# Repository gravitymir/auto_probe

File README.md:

# auto_probe

Отладочные core-платы на STM32 — исходники KiCad, гербера и генератор, который их собирает.

Платы не рисовались мышкой: схема, размещение, разводка и шелкография описаны Python-скриптами
поверх `pcbnew` API. Любую правку можно повторить одной командой, а результат каждый раз
прогоняется через набор проверок.

## Платы

| | STM32G474RE-CoreBoard | STM32H723ZG-CoreBoard |
|---|---|---|
| МК | STM32G474RET6, LQFP64 | STM32H723ZGT6, LQFP144 |
| Размер | 70 × 70 мм | 84 × 84 мм |
| Слоёв | 4 (GND / +3V3 внутренние) | 4 (GND / +3V3 внутренние) |
| Выводы | 4 × гребёнка 1×16, шаг 2.54 | 4 × гребёнка 2×18, шаг 2.54 |
| Питание | USB-C → AP2112K-3.3 | USB-C → AP2112K-3.3 |
| Кварцы | 8 МГц HSE + 32.768 кГц LSE | 25 МГц HSE + 32.768 кГц LSE |
| Отладка | 1×10, распиновка WeAct STLink V2.1 | 1×10, распиновка WeAct STLink V2.1 |
| Формат файлов | KiCad 7 | KiCad 10 |
| Статус | **готова к заказу** | **готова к заказу** |

Все выводы микроконтроллера выведены на гребёнки; шаг 2.54 мм — плата садится в макетку.
У H723 внутренние ряды гребёнок отстоят от центра ровно на 11 × 2.54 мм, то есть
противоположные гребёнки разнесены на 22 шага и плата ложится на сетку 0.1″.

## Что на плате (G474)

**Гребёнки.** J2 — левая, J3 — нижняя, J4 — правая, J5 — верхняя. Назначение каждого
контакта подписано на шелкографии и продублировано в [`PINOUT.csv`](boards/STM32G474RE-CoreBoard/PINOUT.csv).
На каждой гребёнке выведены GND и +3V3 — они подключены к внутренним полигонам через
thermal relief, отдельных дорожек к ним нет.

**J6 — разъём прошивки**, 1×10, распиновка один-в-один с WeAct MiniDebugger / STLink V2.1,
шлейф садится без переходников:

| 1 | 2 | 3 | 4 | 5 | 6 | 7 | 8 | 9 | 10 |
|---|---|---|---|---|---|---|---|---|---|
| 5V | GND | RX (PB6) | TX (PB7) | NRST | SWO (PB3) | GND | SWCLK | SWDIO | 3V3 |

> Контакт 1 (5V) связан с VBUS разъёма USB-C. **USB и отладчик одновременно не подключайте.**

**USB-C (J1)** — не только питание: D+/D− заведены на PA12/PA11, то есть на встроенный
USB 2.0 FS device. Через него работают USB CDC (виртуальный COM-порт) и штатный DFU-бутлоадер
STM32 — прошивка без отладчика вообще. CC1/CC2 притянуты 5.1 кОм к земле (роль устройства).

**Кнопки.** SW1 — RST, SW2 — BOOT0 (для входа в DFU: зажать BOOT, нажать RST).

**Светодиод.** D1 на PA5 (`LED_A`), через 1 кОм.

**R3 (0 Ω)** связывает +3V3 и +3V3A (VDDA / VREF+) в одной точке. Если АЦП будет шуметь —
на это же место ставится ферритовая бусина, переразводить ничего не нужно.

## Чем отличается H723

Раскладка повторяет G474: кристалл смещён к нижнему левому углу (`OFFX` / `OFFY` в
генераторе), поэтому верхнее и правое кольца шире — там и стоят светодиод, кнопки RST и
BOOT, разъём прошивки, USB-C и брендинг. USB-C стоит на плате целиком: корпус упирается
в контур, но за него не свисает.

Электрически устроена так же: те же гребёнки со всеми выводами, тот же USB-C с D+/D− на
встроенный USB FS (PA11/PA12), те же кнопки RST и BOOT0, светодиод (здесь на PB0 через
1 кОм), тот же R3 между +3V3 и +3V3A. Разъём прошивки J6 — тот же 1×10 с распиновкой
WeAct, но UART другой:

| 1 | 2 | 3 | 4 | 5 | 6 | 7 | 8 | 9 | 10 |
|---|---|---|---|---|---|---|---|---|---|
| 5V | GND | RX (PC10) | TX (PC11) | NRST | SWO (PB3) | GND | SWCLK | SWDIO | 3V3 |

Взят USART3 на PC10/PC11, а не USART1: у LQFP144 эта пара выходит на верхнюю гребёнку
рядом со SWCLK, тогда как PA9/PA10 попадают на правую гребёнку за коридором USB-C, куда
дорожку уже не проложить. Ещё из отличий: 25 МГц HSE вместо 8 МГц, две банки VCAP1/VCAP2
по 2.2 мкФ, отдельная развязка VDD33USB и 11 конденсаторов развязки под корпусом вместо 4.

HSE стоит в корпусе SMD-3225 с четырьмя падами: у JLCPCB 25 МГц в нём — Basic Part
(Yangxing X322525MOB4SI, `C9006`), тогда как двухпадовый 5032 только Extended и с
перебоями в наличии. Два лишних пада — экран корпуса, они связаны диагональю под
самим кварцем и посажены на полигон одной via. Нагрузочная ёмкость этого кварца
12 пФ, поэтому обвязка обоих генераторов — 18 пФ; кварц с другой CL ставить нельзя,
частота уйдёт.

Подписан каждый из 144 контактов, оба ряда. У J2, J3 и J5 ряды подписаны с разных сторон
гребёнки — внутренний изнутри, внешний снаружи. Напротив USB-C правое кольцо занято самим
разъёмом и его коридором, поэтому у J4 обе строки остаются слева. Подпись, которой не
хватило места, генератор сам переносит за гребёнку и сообщает об этом в отчёте сборки.
Полная карта — в [`PINOUT.csv`](boards/STM32H723ZG-CoreBoard/PINOUT.csv).

Шрифт шелкографии — 0.8 мм при толщине линии 0.15 мм: это минимум, который JLCPCB
печатает без расплывания. В кольце между гребёнкой и краем платы остаётся 3.7 мм, и
пятизначное имя таким шрифтом туда уже не входит — у нескольких цепей на шелке
короткая форма (`3V3A`, `PC2C`, `USBDP`). В цепях, схеме и `PINOUT.csv` имена полные.

Рядом с деталью печатается только обозначение: под корпусом МК банки развязки стоят
сеткой 3.2 мм, и номиналы читаемым шрифтом там просто не помещаются. Вместо этого на
обратной стороне, в свободных площадках у J4, напечатана таблица «обозначение —
номинал» на все 35 компонентов платы.

Схема H723 нарисована на листе A1: один символ LQFP144 занимает 76 × 188 мм, и вместе с
четырьмя гребёнками 2×18 и 26 конденсаторами на A2 (как у G474) он не раскладывается.

## Как открыть

Футпринты у обеих плат лежат в собственной библиотеке проекта `auto_probe.pretty` рядом с
платой и подключаются через `fp-lib-table` — системные библиотеки KiCad не нужны, и проект
не зависит от того, какая версия KiCad стоит у вас или у сборщика.

```
boards/STM32G474RE-CoreBoard/STM32G474RE-CoreBoard.kicad_pro
boards/STM32H723ZG-CoreBoard/STM32H723ZG-CoreBoard.kicad_pro
```

G474 сохранена в формате KiCad 7 (KiCad 8/9/10 открывают её и конвертируют при первом
сохранении), H723 — в формате KiCad 10: её собирали уже им. Платы независимы, так что
разные форматы никому не мешают, но KiCad 7 файл H723 не откроет.

## Как заказать

Для JLCPCB / PCBWay достаточно одного архива:

```
boards/STM32G474RE-CoreBoard/STM32G474RE-CoreBoard_gerbers.zip
boards/STM32H723ZG-CoreBoard/STM32H723ZG-CoreBoard_gerbers.zip
```

Внутри: 4 слоя меди, паяльная маска, шелкография, паста, контур платы (`.gm1`) и сверловка
(PTH / NPTH раздельно). Параметры заказа: 4 слоя, 1.6 мм, HASL или ENIG, минимальный
зазор 0.2 мм, минимальное отверстие 0.2 мм.

Для монтажа на заводе — `BOM.csv` и `pos.csv` рядом с платой. В BOM G474 проставлены
номера LCSC для микроконтроллера, стабилизатора и USB-C; у H723 — для стабилизатора и
USB-C, номер самого STM32H723ZGT6 подставьте сами. Пассивку подберите из JLCPCB Basic
Parts по номиналу и типоразмеру.

## Генератор

```
gen/
├── kigen.py        разбор библиотек символов, генерация .kicad_sch
├── pcbhelp.py      обёртка над pcbnew: размещение, дорожки, via, полигоны, текст
├── kicadenv.py     где лежат библиотеки KiCad и различия API между версиями
├── build_g474.py   сборка платы G474 целиком
├── build_h723.py   сборка платы H723
├── outputs.py      BOM.csv и PINOUT.csv из готовой платы
├── export.py       гербера, сверловка, pos.csv, PDF и архив для завода
├── drc.py          геометрический контроль зазоров + несоединённые цепи
├── conn.py         связность цепей (union-find)
├── crtyd.py        пересечения courtyard
└── silkchk.py      наложения шелкографии и печать поверх падов
```

Нужен Python с модулем `pcbnew` — от KiCad 7 или KiCad 10 (в Debian/Ubuntu — пакет
`kicad`, в Windows — `C:\Program Files\KiCad\10.0\bin\python.exe`). Каталоги системных
библиотек скрипты находят сами:

```bash
python3 gen/build_h723.py boards/STM32H723ZG-CoreBoard
python3 gen/outputs.py    boards/STM32H723ZG-CoreBoard/STM32H723ZG-CoreBoard.kicad_pcb
python3 gen/export.py     boards/STM32H723ZG-CoreBoard
python3 gen/drc.py        boards/STM32H723ZG-CoreBoard/STM32H723ZG-CoreBoard.kicad_pcb
python3 gen/silkchk.py    boards/STM32H723ZG-CoreBoard/STM32H723ZG-CoreBoard.kicad_pcb
```

`export.py` зовёт `kicad-cli`; им же гоняется штатный DRC:

```bash
kicad-cli pcb drc --schematic-parity --severity-error boards/STM32H723ZG-CoreBoard/STM32H723ZG-CoreBoard.kicad_pcb
```

Позиции надписей, выставленные вручную в KiCad, хранятся в `build_g474.py` в таблицах
`REF_AT` и `VAL_AT` — пересборка их не затирает. Остальные надписи расставляет автоподбор,
который считает занятыми чужие надписи, контуры, **пады** (шелк поверх открытой меди не
печатается) и **корпуса деталей** (иначе надпись уезжает под чип и её не видно).

## Проверки

У KiCad 7 в CLI нет DRC, поэтому проверки написаны отдельно. Текущее состояние обеих плат:

| проверка | G474 | H723 |
|---|---|---|
| зазоры меди | 0 нарушений при штатных 0.2 мм | 0 нарушений при штатных 0.2 мм |
| DRC самого KiCad | 0 ошибок | 0 ошибок |
| схема против платы | — | 0 расхождений |
| несоединённые цепи | 0 | 0 |
| пересечения courtyard | 0 | 0 |
| отверстие-отверстие | минимум 0.387 мм | минимум 0.278 мм |
| наложения шелкографии | 0 | 0 |
| шелкография поверх падов | 0 | 0 |

Обе платы проходят штатный DRC самого KiCad (проверено в KiCad 10) — 0 ошибок при netclass
clearance 0.2 мм. Сигнальные дорожки 0.15 мм, силовые 0.35 мм; минимум JLCPCB для этого
процесса — 0.09 мм. У H723 есть ещё и проверка схемы против платы (`--schematic-parity`),
её умеет только CLI KiCad 10.

Веер из 144 выводов на четыре гребёнки 2×18 упирается не в ширину дорожки, а в угол:
крайние дорожки идут под 42°, и поперёк соседа от шага 0.5 мм остаётся 0.5·cos42° = 0.37 мм.
Отсюда и вынос гребёнок на 27.94 мм от центра — на 26 мм веер в зазор 0.2 мм не укладывался
ни при какой разумной ширине.

## Что осталось

- На D+/D− нет защиты от статики (например, USBLC6-2SC6) — для прототипа терпимо.
- D+/D− заодно выведены на J4 контакты 3 и 4. Удобно для отладки, но это отвод на
  дифференциальной паре: если USB начнёт капризничать при определении — снимите с них всё.
- VBUS не заведён на вывод МК, определить подключение кабеля программно нельзя.

## Лицензия

MIT — см. [LICENSE](LICENSE).

Референсные материалы ST (схемы Nucleo MB1367 / MB1364, их гербера и BOM) в репозиторий
не включены: они распространяются по ST Open Platform License Agreement. Разбор того, что
из них полезно и как это открыть в KiCad, — в [docs/](docs/).

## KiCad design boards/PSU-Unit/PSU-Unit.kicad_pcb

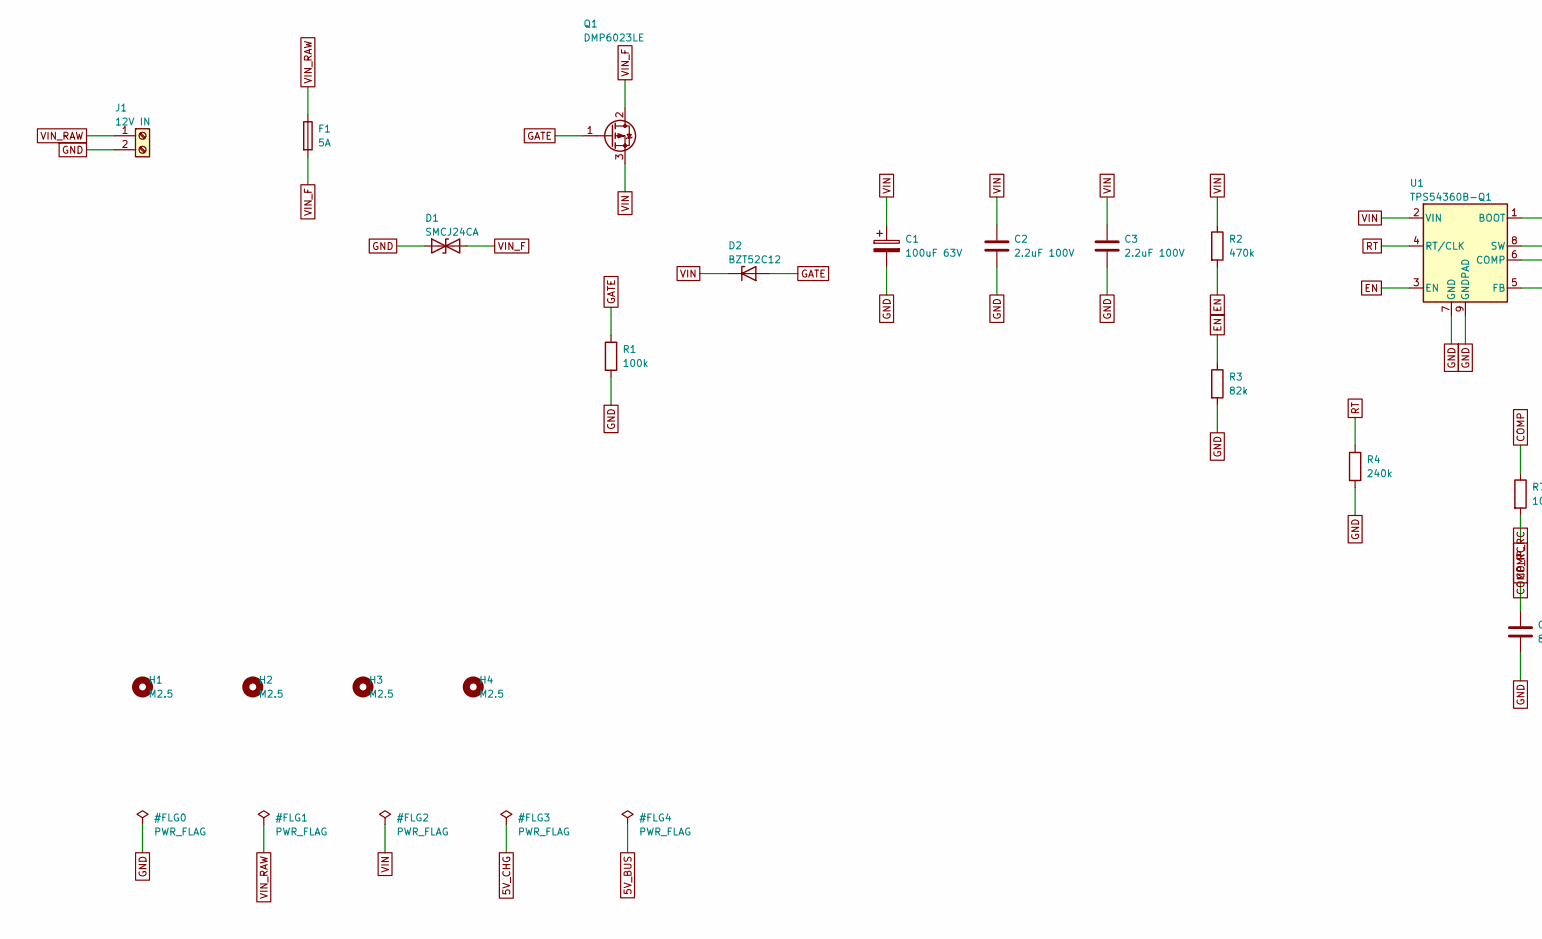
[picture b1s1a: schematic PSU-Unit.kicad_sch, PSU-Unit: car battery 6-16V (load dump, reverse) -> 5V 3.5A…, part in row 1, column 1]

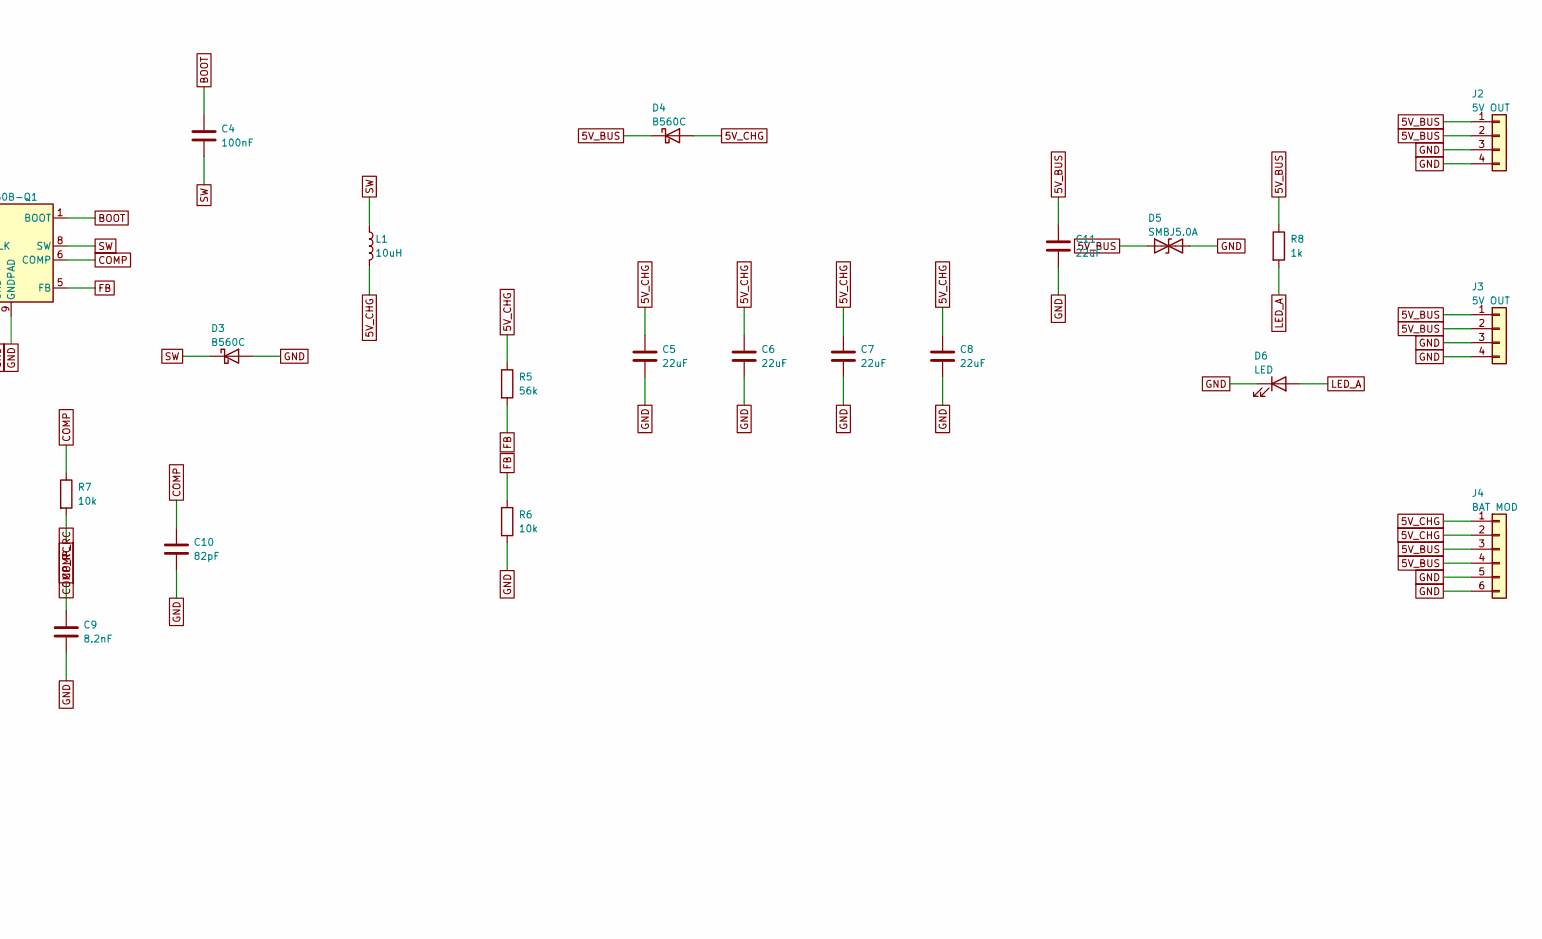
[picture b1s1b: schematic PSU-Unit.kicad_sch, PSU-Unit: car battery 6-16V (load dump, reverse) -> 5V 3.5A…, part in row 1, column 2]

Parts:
C1: 100uF 63V; CP_Elec_10x10
C2, C3: 2.2uF 100V; C_1210_3225Metric
C4: 100nF; C_0402_1005Metric
C5, C6, C7, C8, C11: 22uF; C_1206_3216Metric
C9: 8.2nF; C_0402_1005Metric
C10: 82pF; C_0402_1005Metric
D1: SMCJ24CA; D_SMC
D2: BZT52C12; D_SOD-123
D3, D4: B560C; D_SMC
D5: SMBJ5.0A; D_SMB
D6: LED; LED_0805_2012Metric
F1: 5A; Fuse_Littelfuse_451_2410
H1, H2, H3, H4: M2.5; MountingHole_2.7mm_M2.5
J1: 12V IN; TerminalBlock_Phoenix_MKDS-1,5-2_1x02_P5.00mm_Horizontal
J2, J3: 5V OUT; JST_PH_B4B-PH-K_1x04_P2.00mm_Vertical
J4: BAT MOD; JST_PH_B6B-PH-K_1x06_P2.00mm_Vertical
L1: 10uH; L_TDK_SPM10065VT
Q1: DMP6023LE; SOT-223-3_TabPin2
R1: 100k; R_0402_1005Metric
R2: 470k; R_0402_1005Metric
R3: 82k; R_0402_1005Metric
R4: 240k; R_0402_1005Metric
R5: 56k; R_0402_1005Metric
R6, R7: 10k; R_0402_1005Metric
R8: 1k; R_0402_1005Metric
U1: TPS54360B-Q1; TI_SO-PowerPAD-8_ThermalVias

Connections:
5V_BUS: C11.1, D4.1 (K), D5.1 (A1), J2.1, J2.2, J3.1, J3.2, J4.3, J4.4, R8.1
5V_CHG: C5.1, C6.1, C7.1, C8.1, D4.2 (A), J4.1, J4.2, L1.2, R5.1
BOOT: C4.1, U1.1 (BOOT)
COMP: C10.1, R7.1, U1.6 (COMP)
COMP_RC: C9.1, R7.2
EN: R2.2, R3.1, U1.3 (EN)
FB: R5.2, R6.1, U1.5 (FB)
GATE: D2.2 (A), Q1.1 (G), R1.1
GND: C1.2, C2.2, C3.2, C5.2, C6.2, C7.2, C8.2, C9.2, C10.2, C11.2, D1.1 (A1), D3.2 (A), D5.2 (A2), D6.1 (K), J1.2, J2.3, J2.4, J3.3, J3.4, J4.5, J4.6, R1.2, R3.2, R4.2, R6.2, U1.7 (GND), U1.9 (GNDPAD)
LED_A: D6.2 (A), R8.2
RT: R4.1, U1.4 (RT/CLK)
SW: C4.2, D3.1 (K), L1.1, U1.8 (SW)
VIN: C1.1, C2.1, C3.1, D2.1 (K), Q1.3 (S), R2.1, U1.2 (VIN)
VIN_F: D1.2 (A2), F1.2, Q1.2 (D)
VIN_RAW: F1.1, J1.1

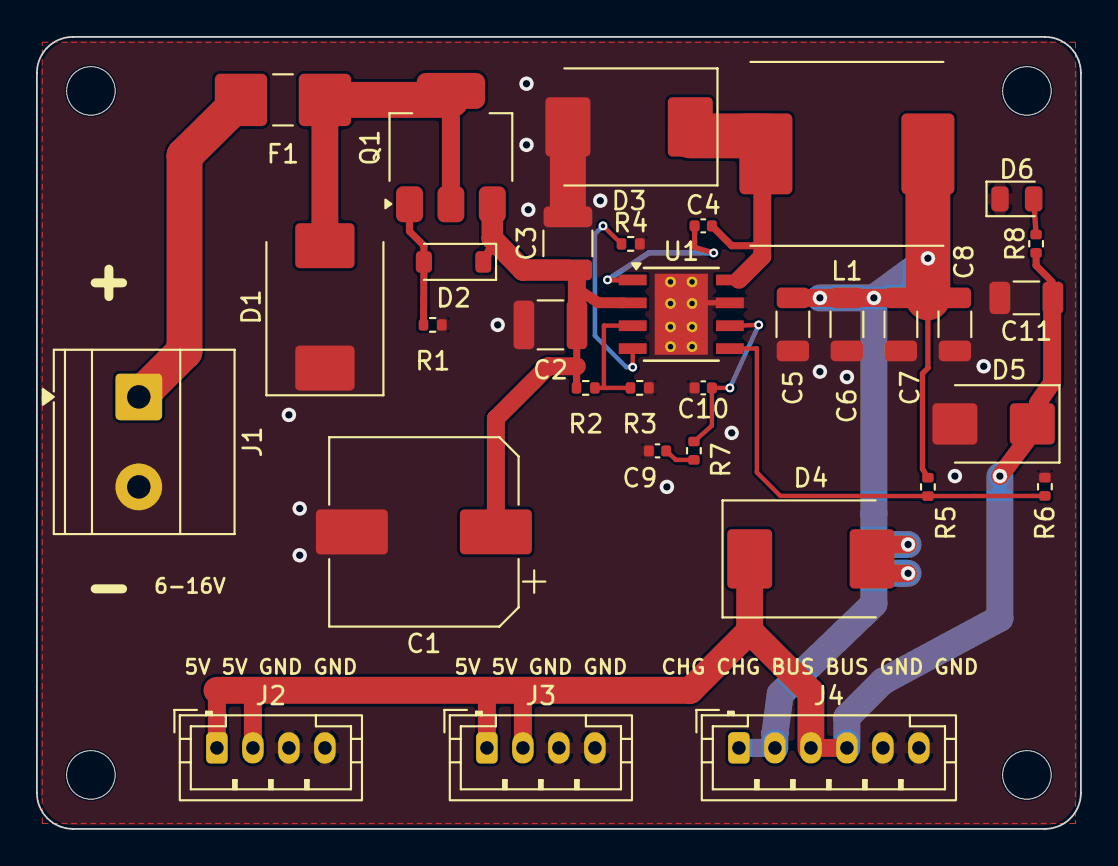
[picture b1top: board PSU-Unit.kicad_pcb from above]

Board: 2 copper layers, 58.0 x 44.0 mm, 37 parts (0 on the bottom side), 15 nets.

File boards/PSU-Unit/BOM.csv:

Comment,Designator,Footprint,LCSC Part #,Qty,Note
100uF 63V,C1,auto_probe:CP_Elec_10x10,C28241,1,проверить наличие на складе
100nF,C4,auto_probe:C_0402_1005Metric,C1525,1,проверить наличие на складе
8.2nF,C9,auto_probe:C_0402_1005Metric,C45186,1,проверить наличие на складе
82pF,C10,auto_probe:C_0402_1005Metric,C45501,1,проверить наличие на складе
22uF,"C11,C5,C6,C7,C8",auto_probe:C_1206_3216Metric,C12891,5,проверить наличие на складе
2.2uF 100V,"C2,C3",auto_probe:C_1210_3225Metric,C55151,2,проверить наличие на складе
SMBJ5.0A,D5,auto_probe:D_SMB,C110528,1,проверить наличие на складе
SMCJ24CA,D1,auto_probe:D_SMC,C151279,1,проверить наличие на складе
B560C,"D3,D4",auto_probe:D_SMC,C85100,2,проверить наличие на складе
BZT52C12,D2,auto_probe:D_SOD-123,C124196,1,проверить наличие на складе
5A,F1,auto_probe:Fuse_Littelfuse_451_2410,C48467,1,проверить наличие на складе
5V OUT,"J2,J3",auto_probe:JST_PH_B4B-PH-K_1x04_P2.00mm_Vertical,C131334,2,проверить наличие на складе
BAT MOD,J4,auto_probe:JST_PH_B6B-PH-K_1x06_P2.00mm_Vertical,C131342,1,проверить наличие на складе
LED,D6,auto_probe:LED_0805_2012Metric,C84256,1,проверить наличие на складе
10uH,L1,auto_probe:L_TDK_SPM10065VT,C5119327,1,проверить наличие на складе
1k,R8,auto_probe:R_0402_1005Metric,C11702,1,проверить наличие на складе
100k,R1,auto_probe:R_0402_1005Metric,C25741,1,проверить наличие на складе
10k,"R6,R7",auto_probe:R_0402_1005Metric,C25744,2,проверить наличие на складе
470k,R2,auto_probe:R_0402_1005Metric,C25790,1,проверить наличие на складе
56k,R5,auto_probe:R_0402_1005Metric,C25796,1,проверить наличие на складе
82k,R3,auto_probe:R_0402_1005Metric,C4142,1,проверить наличие на складе
240k,R4,auto_probe:R_0402_1005Metric,C64043,1,проверить наличие на складе
DMP6023LE,Q1,auto_probe:SOT-223-3_TabPin2,C154901,1,проверить наличие на складе
TPS54360B-Q1,U1,auto_probe:TI_SO-PowerPAD-8_ThermalVias,C2687968,1,проверить наличие на складе
12V IN,J1,"auto_probe:TerminalBlock_Phoenix_MKDS-1,5-2_1x02_P5.00mm_Horizontal",C474881,1,проверить наличие на складе

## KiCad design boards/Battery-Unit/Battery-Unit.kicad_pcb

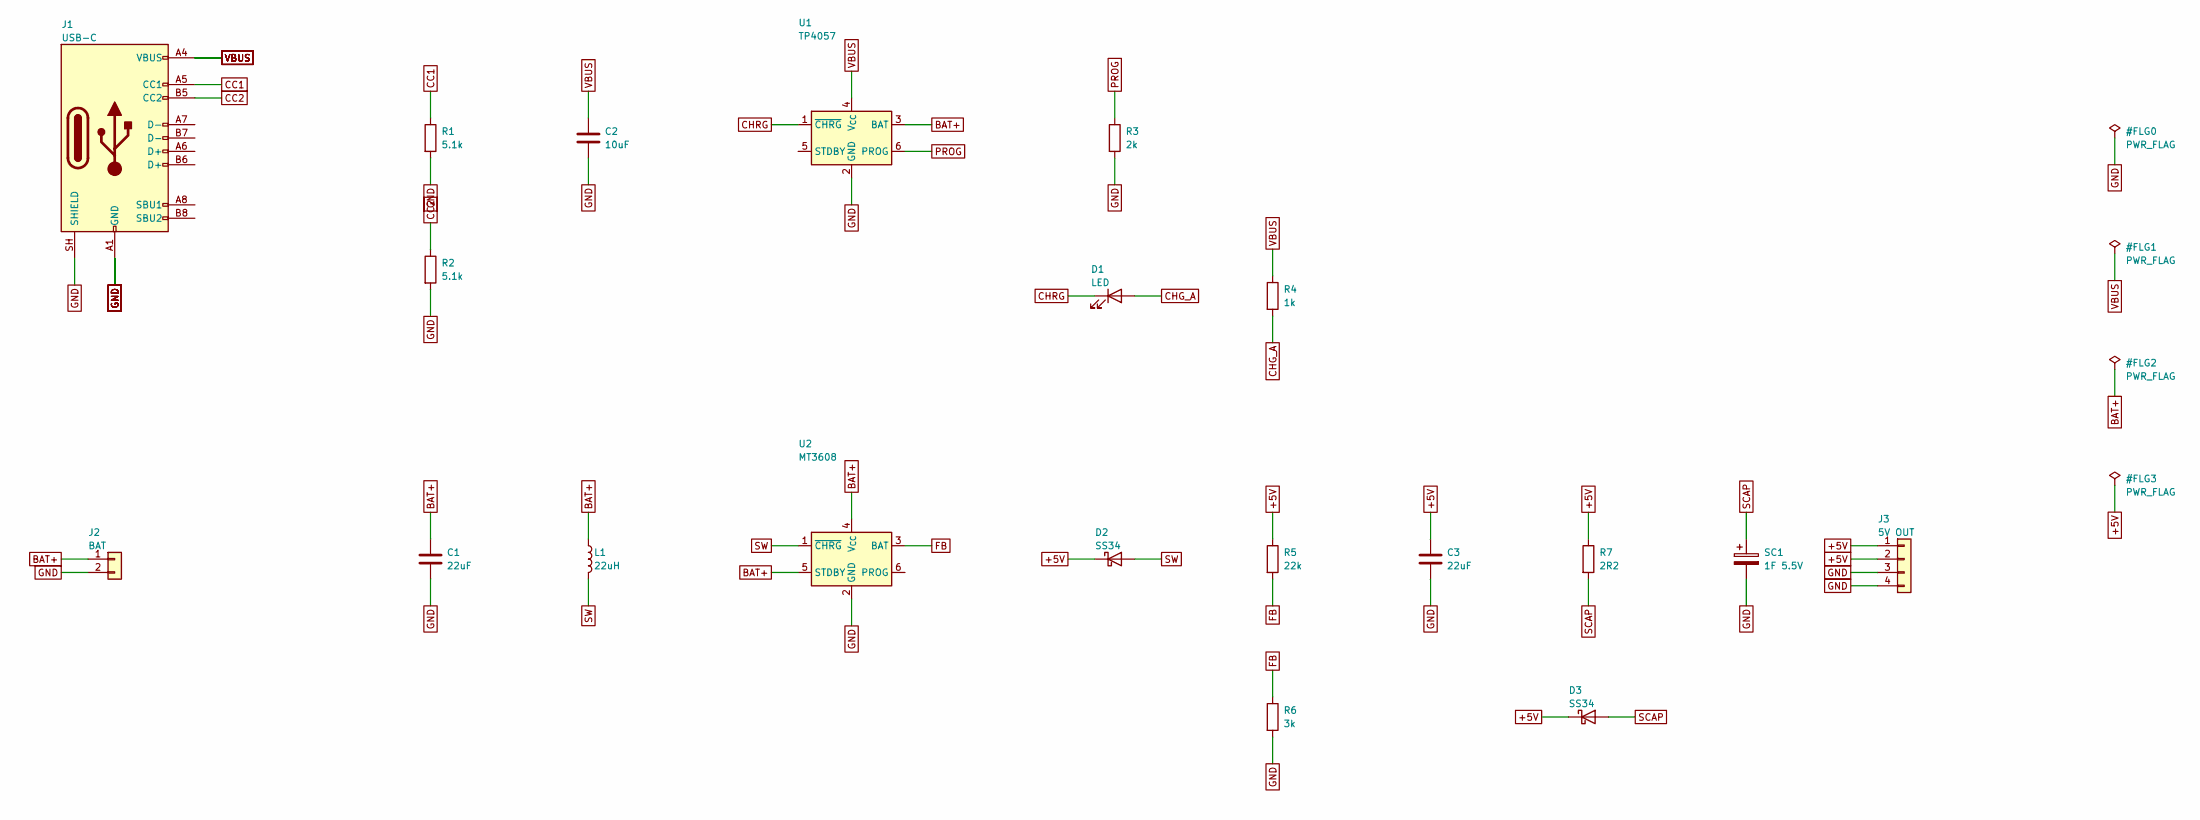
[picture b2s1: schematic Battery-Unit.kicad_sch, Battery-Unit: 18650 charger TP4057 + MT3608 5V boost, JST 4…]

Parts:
C1, C3: 22uF; C_0805_2012Metric
C2: 10uF; C_0805_2012Metric
D1: LED; LED_0805_2012Metric
D2, D3: SS34; D_SMA
J1: USB-C; USB_C_Receptacle_HRO_TYPE-C-31-M-12
J2: BAT; JST_PH_B2B-PH-K_1x02_P2.00mm_Vertical
J3: 5V OUT; JST_PH_B4B-PH-K_1x04_P2.00mm_Vertical
L1: 22uH; L_Taiyo-Yuden_NR-40xx
R1, R2: 5.1k; R_0402_1005Metric
R3: 2k; R_0402_1005Metric
R4: 1k; R_0402_1005Metric
R5: 22k; R_0402_1005Metric
R6: 3k; R_0402_1005Metric
R7: 2R2; R_0402_1005Metric
SC1: 1F 5.5V; CP_Radial_D10.0mm_P5.00mm
U1: TP4057; SOT-23-6
U2: MT3608; SOT-23-6

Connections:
+5V: C3.1, D2.1 (K), D3.1 (K), J3.1, J3.2, R5.1, R7.1
BAT+: C1.1, J2.1, L1.1, U1.3 (BAT), U2.4 (V_{CC}), U2.5 (STDBY)
CC1: J1.A5 (CC1), R1.1
CC2: J1.B5 (CC2), R2.1
CHG_A: D1.2 (A), R4.2
CHRG: D1.1 (K), U1.1 (~CHRG)
FB: R5.2, R6.1, U2.3 (BAT)
GND: C1.2, C2.2, C3.2, J1.A1 (GND), J1.A12 (GND), J1.B1 (GND), J1.B12 (GND), J1.SH (SHIELD), J2.2, J3.3, J3.4, R1.2, R2.2, R3.2, R6.2, SC1.2, U1.2 (GND), U2.2 (GND)
PROG: R3.1, U1.6 (PROG)
SCAP: D3.2 (A), R7.2, SC1.1
SW: D2.2 (A), L1.2, U2.1 (~CHRG)
VBUS: C2.1, J1.A4 (VBUS), J1.A9 (VBUS), J1.B4 (VBUS), J1.B9 (VBUS), R4.1, U1.4 (V_{CC})

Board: 2 copper layers, 20 parts (0 on the bottom side), 12 nets, no tracks yet.

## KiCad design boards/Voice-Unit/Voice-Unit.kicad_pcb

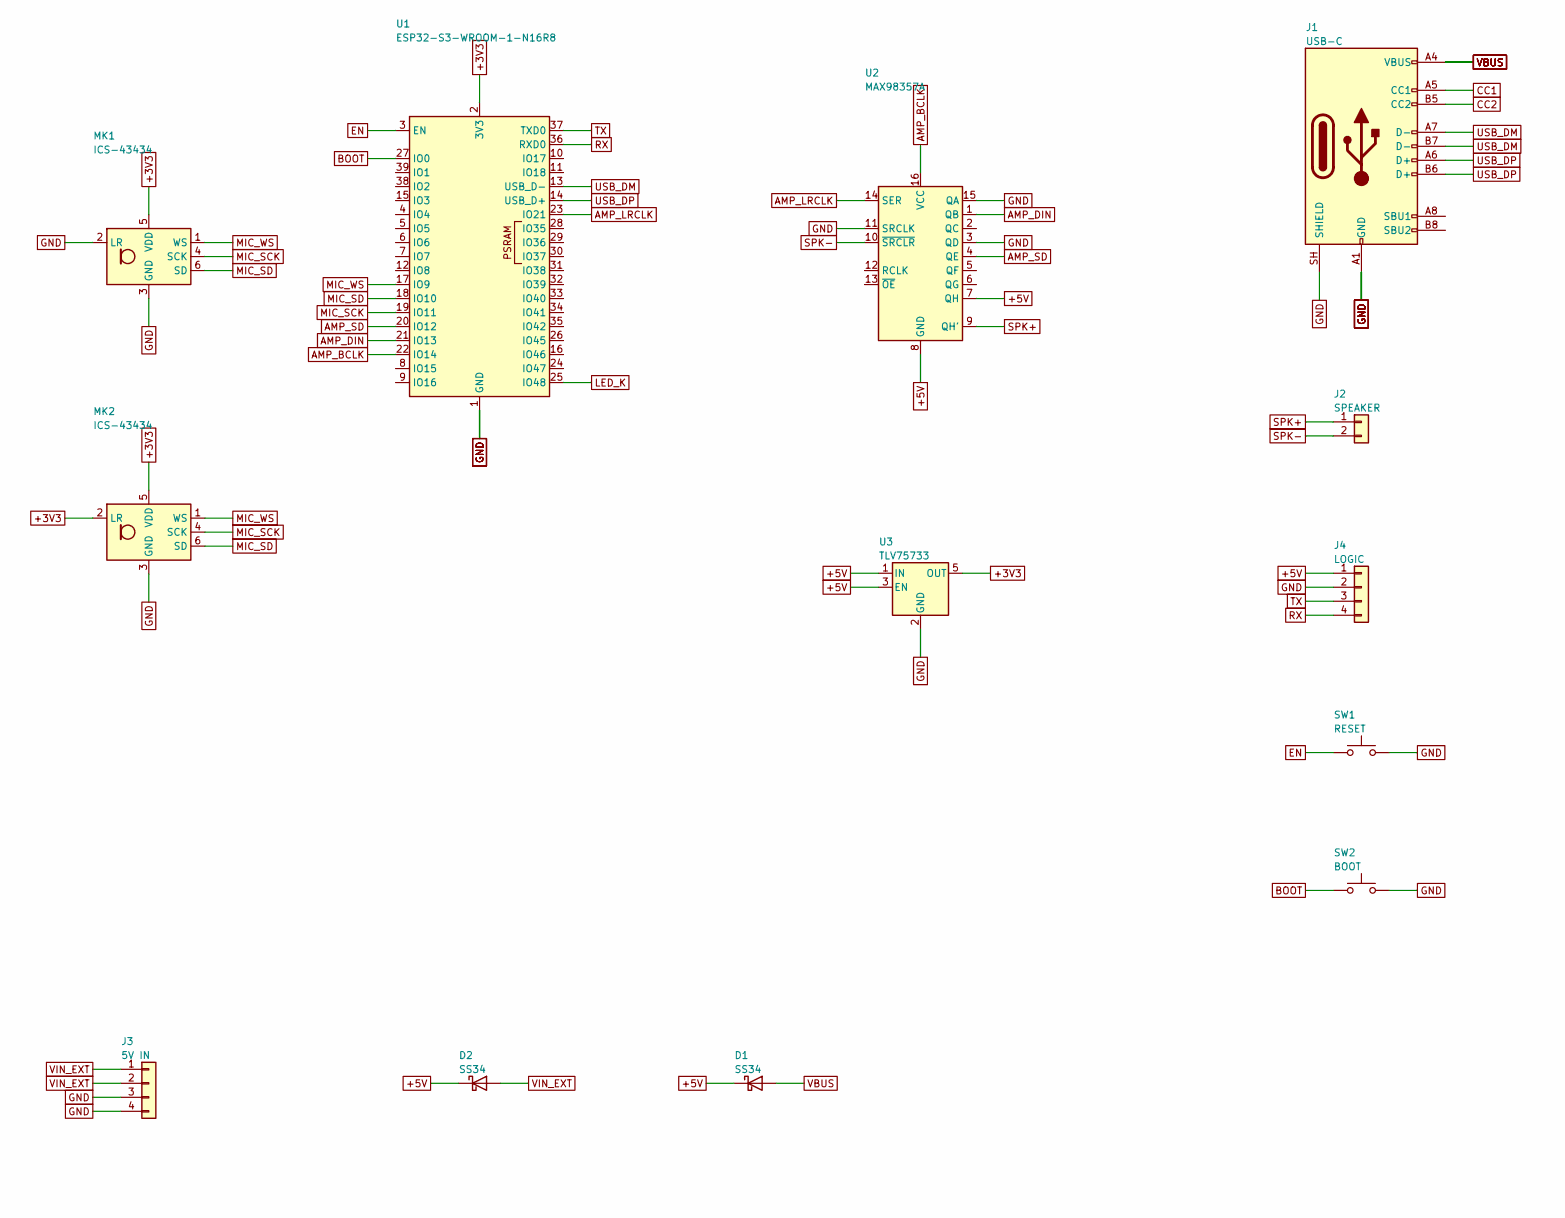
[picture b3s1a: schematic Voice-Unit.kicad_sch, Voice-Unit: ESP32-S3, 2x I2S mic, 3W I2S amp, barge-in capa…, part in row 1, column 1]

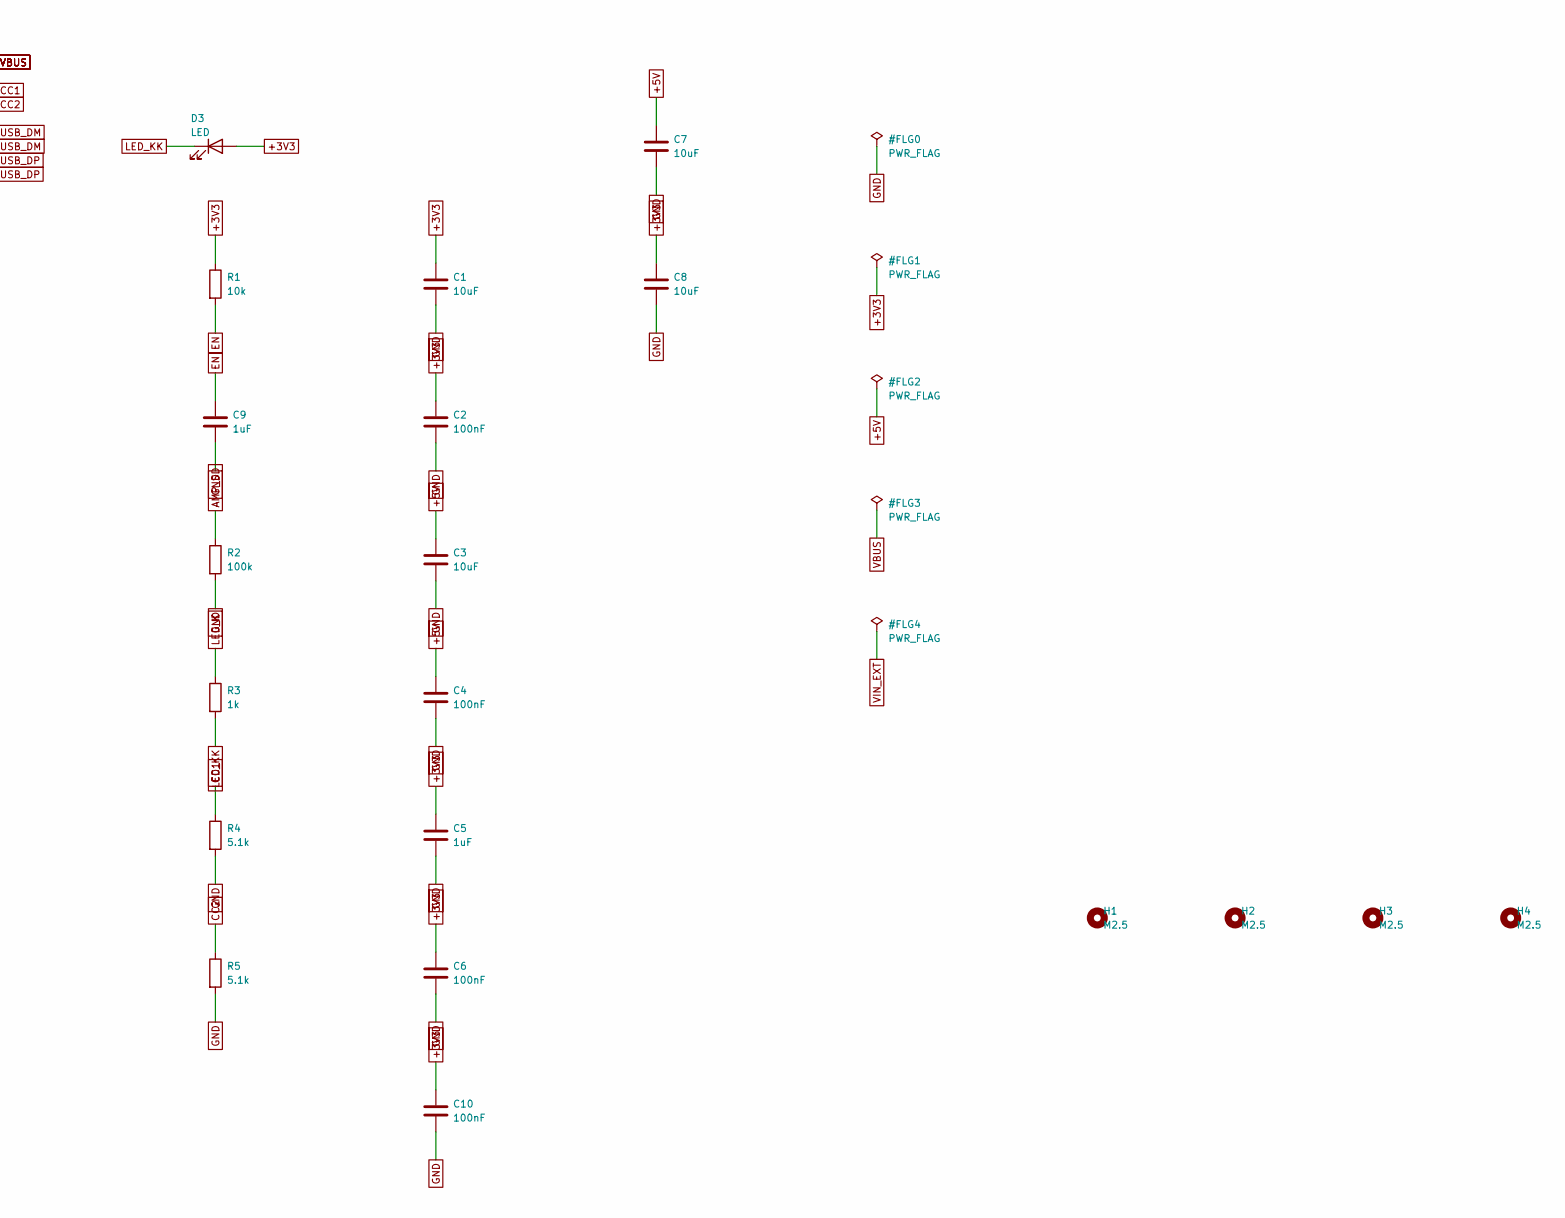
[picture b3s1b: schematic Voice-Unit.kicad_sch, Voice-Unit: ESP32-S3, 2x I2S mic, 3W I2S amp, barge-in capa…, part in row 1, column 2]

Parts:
C1, C3, C7, C8: 10uF; C_0805_2012Metric
C2, C4, C6, C10: 100nF; C_0402_1005Metric
C5, C9: 1uF; C_0402_1005Metric
D1, D2: SS34; D_SMA
D3: LED; LED_0805_2012Metric
H1, H2, H3, H4: M2.5; MountingHole_2.7mm_M2.5
J1: USB-C; USB_C_Receptacle_HRO_TYPE-C-31-M-12
J2: SPEAKER; PinHeader_1x02_P2.54mm_Vertical
J3: 5V IN; JST_PH_B4B-PH-K_1x04_P2.00mm_Vertical
J4: LOGIC; PinHeader_1x04_P2.54mm_Vertical
MK1, MK2: ICS-43434; InvenSense_ICS-43434-6_3.5x2.65mm
R1: 10k; R_0402_1005Metric
R2: 100k; R_0402_1005Metric
R3: 1k; R_0402_1005Metric
R4, R5: 5.1k; R_0402_1005Metric
SW1: RESET; SW_SPST_SKQG_WithoutStem
SW2: BOOT; SW_SPST_SKQG_WithoutStem
U1: ESP32-S3-WROOM-1-N16R8; ESP32-S3-WROOM-1
U2: MAX98357A; TQFN-16-1EP_3x3mm_P0.5mm_EP1.6x1.6mm
U3: TLV75733; SOT-23-5

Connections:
+3V3: C1.1, C2.1, C5.1, C6.1, C8.1, C10.1, D3.2 (A), MK1.5 (VDD), MK2.2 (LR), MK2.5 (VDD), R1.1, U1.2 (3V3), U3.5 (OUT)
+5V: C3.1, C4.1, C7.1, D1.1 (K), D2.1 (K), J4.1, U2.7 (QH), U2.8 (GND), U3.1 (IN), U3.3 (EN)
AMP_BCLK: U1.22 (IO14), U2.16 (VCC)
AMP_DIN: U1.21 (IO13), U2.1 (QB)
AMP_LRCLK: U1.23 (IO21), U2.14 (SER)
AMP_SD: R2.1, U1.20 (IO12), U2.4 (QE)
BOOT: SW2.1, U1.27 (IO0)
CC1: J1.A5 (CC1), R4.1
CC2: J1.B5 (CC2), R5.1
EN: C9.1, R1.2, SW1.1, U1.3 (EN)
GND: C1.2, C2.2, C3.2, C4.2, C5.2, C6.2, C7.2, C8.2, C9.2, C10.2, J1.A1 (GND), J1.A12 (GND), J1.B1 (GND), J1.B12 (GND), J1.SH (SHIELD), J3.3, J3.4, J4.2, MK1.2 (LR), MK1.3 (GND), MK2.3 (GND), R2.2, R4.2, R5.2, SW1.2, SW2.2, U1.1 (GND), U1.40 (GND), U1.41 (GND), U2.3 (QD), U2.11 (SRCLK), U2.15 (QA), U2.17, U3.2 (GND)
LED_K: R3.1, U1.25 (IO48)
LED_KK: D3.1 (K), R3.2
MIC_SCK: MK1.4 (SCK), MK2.4 (SCK), U1.19 (IO11)
MIC_SD: MK1.6 (SD), MK2.6 (SD), U1.18 (IO10)
MIC_WS: MK1.1 (WS), MK2.1 (WS), U1.17 (IO9)
RX: J4.4, U1.36 (RXD0)
SPK+: J2.1, U2.9 (QH')
SPK-: J2.2, U2.10 (~SRCLR)
TX: J4.3, U1.37 (TXD0)
USB_DM: J1.A7 (D-), J1.B7 (D-), U1.13 (USB_D-)
USB_DP: J1.A6 (D+), J1.B6 (D+), U1.14 (USB_D+)
VBUS: D1.2 (A), J1.A4 (VBUS), J1.A9 (VBUS), J1.B4 (VBUS), J1.B9 (VBUS)
VIN_EXT: D2.2 (A), J3.1, J3.2

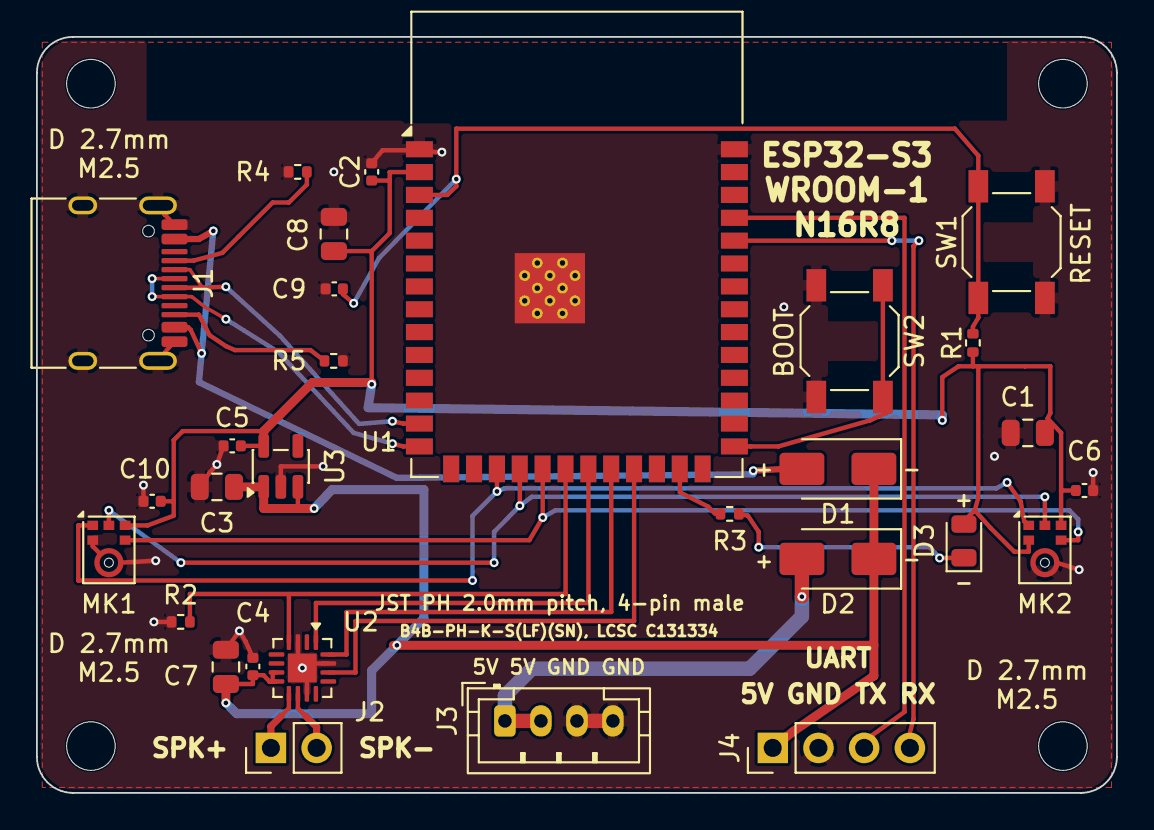
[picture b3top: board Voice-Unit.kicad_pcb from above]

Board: 2 copper layers, 60.0 x 42.0 mm, 33 parts (0 on the bottom side), 24 nets.

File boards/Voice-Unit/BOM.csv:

Comment,Designator,Footprint,LCSC Part #,Qty,Note
100nF,"C10,C2,C4,C6",auto_probe:C_0402_1005Metric,C1525,4,проверить наличие на складе
1uF,"C5,C9",auto_probe:C_0402_1005Metric,C52923,2,проверить наличие на складе
10uF,"C1,C3,C7,C8",auto_probe:C_0805_2012Metric,C15850,4,проверить наличие на складе
SS34,"D1,D2",auto_probe:D_SMA,C8678,2,проверить наличие на складе
ESP32-S3-WROOM-1-N16R8,U1,auto_probe:ESP32-S3-WROOM-1,C2913202,1,проверить наличие на складе
ICS-43434,"MK1,MK2",auto_probe:InvenSense_ICS-43434-6_3.5x2.65mm,C5656610,2,проверить наличие на складе
5V IN,J3,auto_probe:JST_PH_B4B-PH-K_1x04_P2.00mm_Vertical,C131334,1,проверить наличие на складе
LED,D3,auto_probe:LED_0805_2012Metric,C84256,1,проверить наличие на складе
SPEAKER,J2,auto_probe:PinHeader_1x02_P2.54mm_Vertical,,1,"выводная: в SMT-монтаж не идёт, паяется отдельно"
LOGIC,J4,auto_probe:PinHeader_1x04_P2.54mm_Vertical,,1,"выводная: в SMT-монтаж не идёт, паяется отдельно"
1k,R3,auto_probe:R_0402_1005Metric,C11702,1,проверить наличие на складе
100k,R2,auto_probe:R_0402_1005Metric,C25741,1,проверить наличие на складе
10k,R1,auto_probe:R_0402_1005Metric,C25744,1,проверить наличие на складе
5.1k,"R4,R5",auto_probe:R_0402_1005Metric,C25905,2,проверить наличие на складе
TLV75733,U3,auto_probe:SOT-23-5,C485517,1,проверить наличие на складе
BOOT/RESET,"SW1,SW2",auto_probe:SW_SPST_SKQG_WithoutStem,C318884,2,проверить наличие на складе
MAX98357A,U2,auto_probe:TQFN-16-1EP_3x3mm_P0.5mm_EP1.6x1.6mm,C910544,1,проверить наличие на складе
USB-C,J1,auto_probe:USB_C_Receptacle_HRO_TYPE-C-31-M-12,C165948,1,проверить наличие на складе

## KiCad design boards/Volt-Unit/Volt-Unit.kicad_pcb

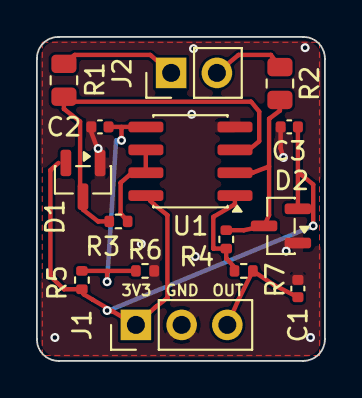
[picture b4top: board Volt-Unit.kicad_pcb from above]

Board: 2 copper layers, 16.0 x 18.0 mm, 15 parts (0 on the bottom side), 10 nets.

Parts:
C1: 470pF; C_0402_1005Metric
C2, C3: 100nF; C_0402_1005Metric
D1, D2: BAT54S; SOT-23
J1: LOGIC; PinHeader_1x03_P2.54mm_Vertical
J2: PROBE; PinHeader_1x02_P2.54mm_Vertical
R1, R2: 470k; R_0805_2012Metric
R3, R4: 18k; R_0402_1005Metric
R5, R6: 10k; R_0402_1005Metric
R7: 220R; R_0402_1005Metric
U1: LMV358; SOIC-8_3.9x4.9mm_P1.27mm

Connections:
+3V3: C3.1, D1.2, D2.2, J1.1, R5.1, U1.8
AOUT: R4.2, R7.1, U1.1
FB: D2.3, R2.2, R4.1, U1.2
GND: C1.2, C2.2, C3.2, D1.1, D2.1, J1.2, R6.2, U1.4
INP: D1.3, R1.2, R3.1, U1.3
OUT: C1.1, J1.3, R7.2
VIN+: J2.1, R1.1
VIN-: J2.2, R2.1
VREF: R3.2, U1.6, U1.7
VREFD: C2.1, R5.2, R6.1, U1.5

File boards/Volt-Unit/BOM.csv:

Comment,Designator,Footprint,LCSC Part #,Qty,Note
100nF,"C2,C3",auto_probe:C_0402_1005Metric,C1525,2,проверить наличие на складе
470pF,C1,auto_probe:C_0402_1005Metric,C75274,1,проверить наличие на складе
PROBE,J2,auto_probe:PinHeader_1x02_P2.54mm_Vertical,,1,"выводная: в SMT-монтаж не идёт, паяется отдельно"
LOGIC,J1,auto_probe:PinHeader_1x03_P2.54mm_Vertical,,1,"выводная: в SMT-монтаж не идёт, паяется отдельно"
220R,R7,auto_probe:R_0402_1005Metric,C25091,1,проверить наличие на складе
10k,"R5,R6",auto_probe:R_0402_1005Metric,C25744,2,проверить наличие на складе
18k,"R3,R4",auto_probe:R_0402_1005Metric,C25762,2,проверить наличие на складе
470k,"R1,R2",auto_probe:R_0805_2012Metric,C17709,2,проверить наличие на складе
LMV358,U1,auto_probe:SOIC-8_3.9x4.9mm_P1.27mm,C7980,1,проверить наличие на складе
BAT54S,"D1,D2",auto_probe:SOT-23,C47546,2,проверить наличие на складе

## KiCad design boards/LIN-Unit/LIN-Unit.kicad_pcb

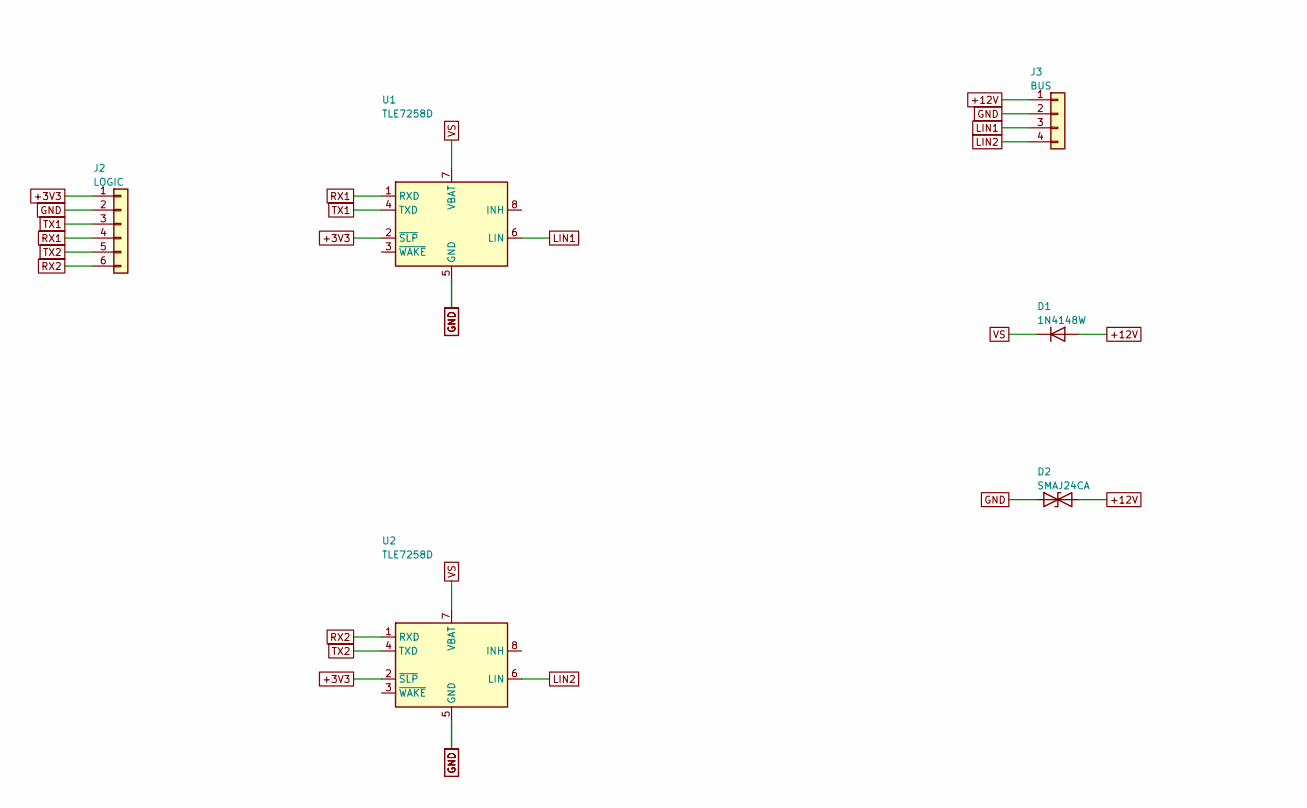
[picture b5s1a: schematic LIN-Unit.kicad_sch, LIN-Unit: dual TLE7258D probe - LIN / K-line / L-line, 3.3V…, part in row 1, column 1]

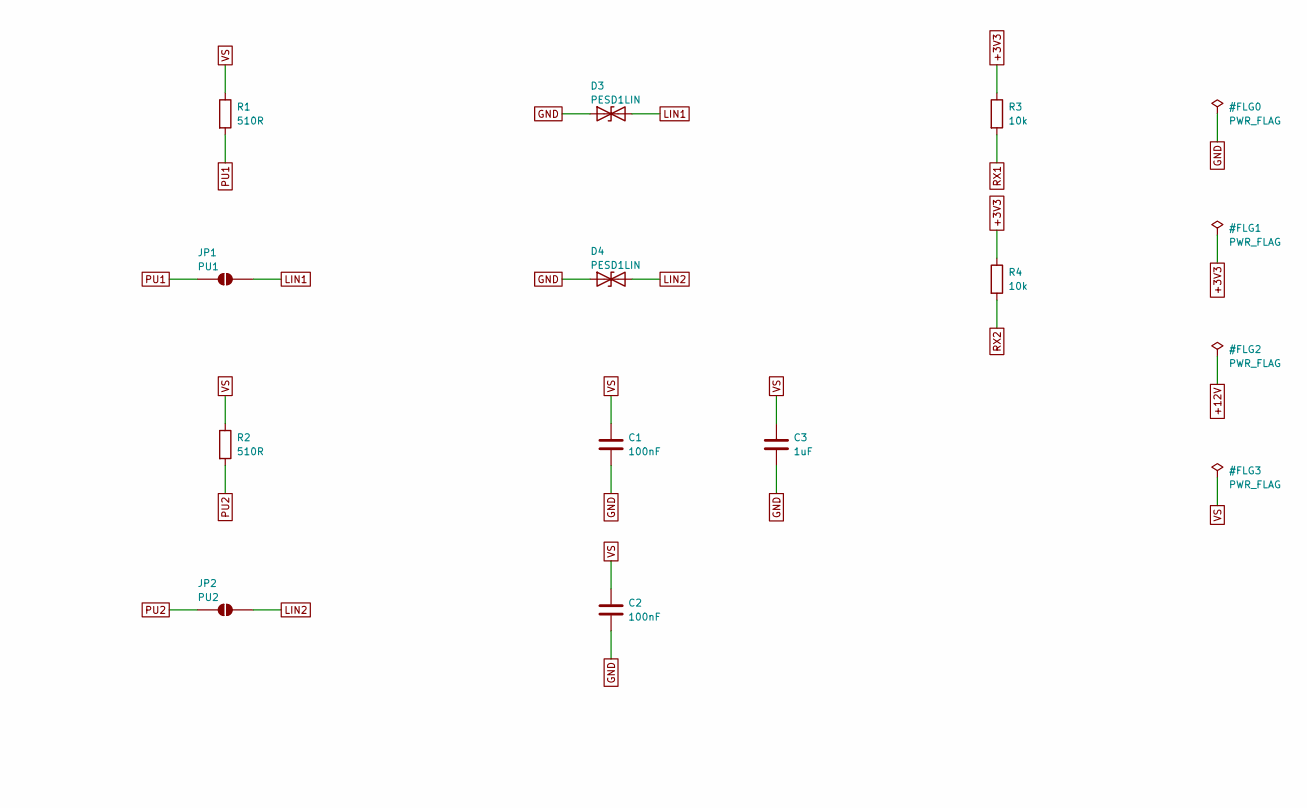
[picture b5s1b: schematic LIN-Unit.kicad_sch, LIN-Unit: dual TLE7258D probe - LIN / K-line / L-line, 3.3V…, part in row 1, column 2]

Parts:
C1, C2: 100nF; C_0402_1005Metric
C3: 1uF; C_0603_1608Metric
D1: 1N4148W; D_SOD-123
D2: SMAJ24CA; D_SMA
D3, D4: PESD1LIN; D_SOD-323
J2: LOGIC; PinHeader_1x06_P2.54mm_Vertical
J3: BUS; PinHeader_1x04_P2.54mm_Vertical
JP1: PU1; SolderJumper-2_P1.3mm_Open_TrianglePad1.0x1.5mm
JP2: PU2; SolderJumper-2_P1.3mm_Open_TrianglePad1.0x1.5mm
R1, R2: 510R; R_0805_2012Metric
R3, R4: 10k; R_0402_1005Metric
U1, U2: TLE7258D; VSON-8-1EP_3x3mm_P0.65mm_EP1.6x2.4mm

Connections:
+3V3: J2.1, R3.1, R4.1, U1.2 (~SLP), U2.2 (~SLP)
+12V: D1.2 (A), D2.2 (A2), J3.1
GND: C1.2, C2.2, C3.2, D2.1 (A1), D3.1 (A1), D4.1 (A1), J2.2, J3.2, U1.5 (GND), U1.9 (GND), U2.5 (GND), U2.9 (GND)
LIN1: D3.2 (A2), J3.3, JP1.2 (B), U1.6 (LIN)
LIN2: D4.2 (A2), J3.4, JP2.2 (B), U2.6 (LIN)
PU1: JP1.1 (A), R1.2
PU2: JP2.1 (A), R2.2
RX1: J2.4, R3.2, U1.1 (RXD)
RX2: J2.6, R4.2, U2.1 (RXD)
TX1: J2.3, U1.4 (TXD)
TX2: J2.5, U2.4 (TXD)
VS: C1.1, C2.1, C3.1, D1.1 (K), R1.1, R2.1, U1.7 (VBAT), U2.7 (VBAT)
